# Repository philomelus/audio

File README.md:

# audio
Various audio circuits I've drawn up, almost exclusively found elsewhere.

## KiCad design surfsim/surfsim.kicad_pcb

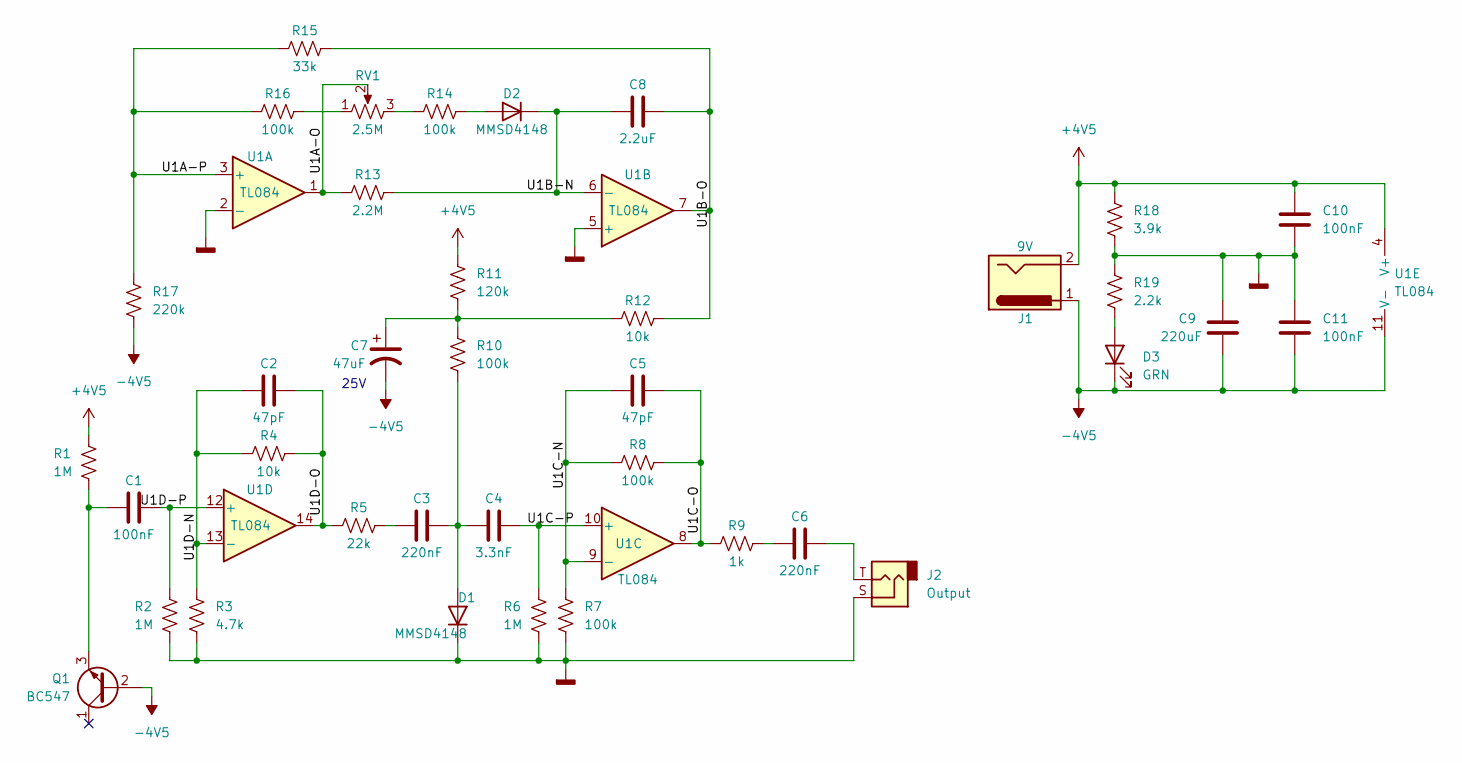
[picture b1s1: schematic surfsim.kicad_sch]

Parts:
C1, C10, C11: 100nF; C_0805_2012Metric_Pad1.18x1.45mm_HandSolder
C2, C5: 47pF; C_0805_2012Metric_Pad1.18x1.45mm_HandSolder
C3, C6: 220nF; C_0805_2012Metric_Pad1.18x1.45mm_HandSolder
C4: 3.3nF; C_0805_2012Metric_Pad1.18x1.45mm_HandSolder
C7: 47uF; C_0805_2012Metric_Pad1.18x1.45mm_HandSolder
C8: 2.2uF; C_0805_2012Metric_Pad1.18x1.45mm_HandSolder
C9: 220uF; C_0805_2012Metric_Pad1.18x1.45mm_HandSolder
D1, D2: MMSD4148; D_SOD-123
D3: GRN; D_1206_3216Metric_Pad1.42x1.75mm_HandSolder
J1: 9V; BarrelJack_CUI_PJ-036AH-SMT_Horizontal
J2: Output; Jack_3.5mm_CUI_MJ-3523-SMT
Q1: BC547; TO-92_Inline
R1, R2, R6: 1M; R_0805_2012Metric_Pad1.20x1.40mm_HandSolder
R3: 4.7k; R_0805_2012Metric_Pad1.20x1.40mm_HandSolder
R4, R12: 10k; R_0805_2012Metric_Pad1.20x1.40mm_HandSolder
R5: 22k; R_0805_2012Metric_Pad1.20x1.40mm_HandSolder
R7, R8, R10, R14, R16: 100k; R_0805_2012Metric_Pad1.20x1.40mm_HandSolder
R9: 1k; R_0805_2012Metric_Pad1.20x1.40mm_HandSolder
R11: 120k; R_0805_2012Metric_Pad1.20x1.40mm_HandSolder
R13: 2.2M; R_0805_2012Metric_Pad1.20x1.40mm_HandSolder
R15: 33k; R_0805_2012Metric_Pad1.20x1.40mm_HandSolder
R17: 220k; R_0805_2012Metric_Pad1.20x1.40mm_HandSolder
R18: 3.9k; R_0805_2012Metric_Pad1.20x1.40mm_HandSolder
R19: 2.2k; R_0805_2012Metric_Pad1.20x1.40mm_HandSolder
RV1: 2.5M; SolderWire-0.1sqmm_1x03_P3.6mm_D0.4mm_OD1mm
U1: TL084; SOIC-14_3.9x8.7mm_P1.27mm

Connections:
+4V5: C10.1, J1.2, R1.1, R11.1, R18.1, U1.4 (V+)
-4V5: C7.2, C9.2, C11.2, D3.1 (K), J1.1, Q1.2 (B), R17.2, U1.11 (V-)
/U1A-O: R13.1, RV1.2, U1.1
/U1A-P: R15.1, R16.1, R17.1, U1.3 (+)
/U1B-N: C8.1, D2.1 (K), R13.2, U1.6 (-)
/U1B-O: C8.2, R12.2, R15.2, U1.7
/U1C-N: C5.1, R7.1, R8.1, U1.9 (-)
/U1C-O: C5.2, R8.2, R9.1, U1.8
/U1C-P: C4.2, R6.1, U1.10 (+)
/U1D-N: C2.1, R3.1, R4.1, U1.13 (-)
/U1D-O: C2.2, R4.2, R5.1, U1.14
/U1D-P: C1.2, R2.1, U1.12 (+)
GNDD: C9.1, C10.2, C11.1, D1.1 (K), J2.S, R2.2, R3.2, R6.2, R7.2, R18.2, R19.1, U1.2 (-), U1.5 (+)
unnamed: C1.1, Q1.3 (E), R1.2
unnamed: C3.1, R5.2
unnamed: C3.2, C4.1, D1.2 (A), R10.2
unnamed: C6.1, R9.2
unnamed: C6.2, J2.T
unnamed: C7.1, R10.1, R11.2, R12.1
unnamed: D2.2 (A), R14.2
unnamed: D3.2 (A), R19.2
unnamed: R14.1, RV1.3
unnamed: R16.2, RV1.1

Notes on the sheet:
25V

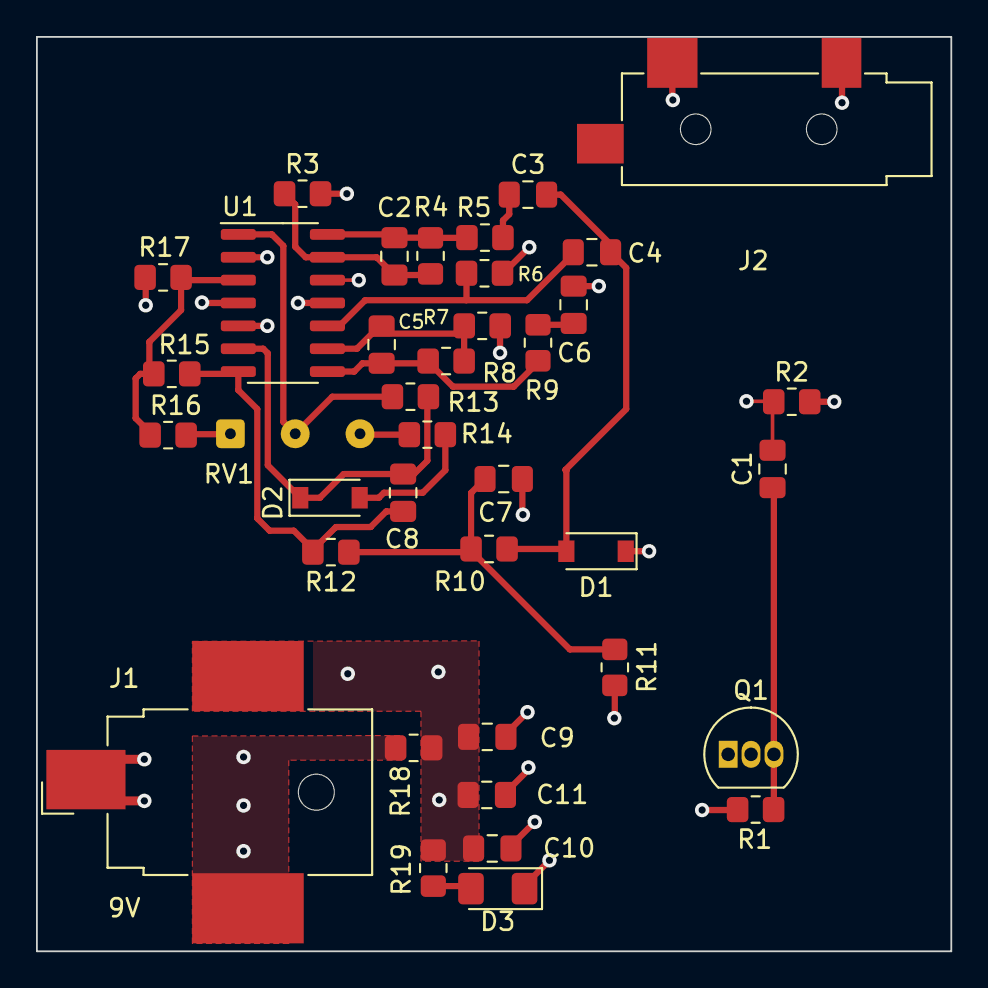
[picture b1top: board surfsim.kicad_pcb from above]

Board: 4 copper layers, 50.8 x 50.8 mm, 38 parts (0 on the bottom side), 23 nets.

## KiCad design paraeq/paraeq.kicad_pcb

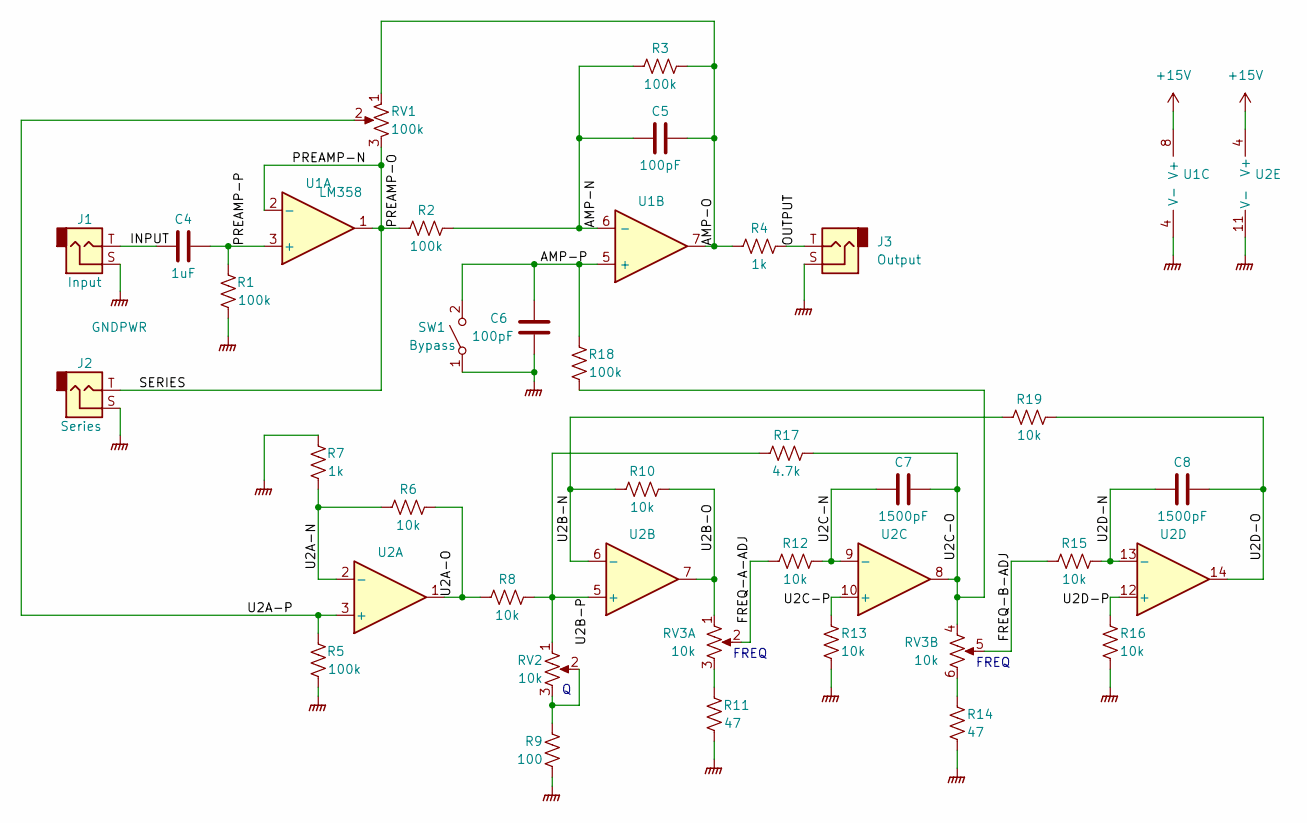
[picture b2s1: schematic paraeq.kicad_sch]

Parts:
C4: 1uF; C_0805_2012Metric_Pad1.18x1.45mm_HandSolder
C5, C6: 100pF; C_0805_2012Metric_Pad1.18x1.45mm_HandSolder
C7, C8: 1500pF; C_0805_2012Metric_Pad1.18x1.45mm_HandSolder
J1: Input; Jack_3.5mm_CUI_SJ1-3523N_Horizontal
J2: Series; Jack_3.5mm_CUI_SJ1-3523N_Horizontal
J3: Output; Jack_3.5mm_CUI_SJ1-3523N_Horizontal
R1, R2, R3, R5, R18: 100k; R_0805_2012Metric_Pad1.20x1.40mm_HandSolder
R4, R7: 1k; R_0805_2012Metric_Pad1.20x1.40mm_HandSolder
R6, R8, R10, R12, R13, R15, R16, R19: 10k; R_0805_2012Metric_Pad1.20x1.40mm_HandSolder
R9: 100; R_0805_2012Metric_Pad1.20x1.40mm_HandSolder
R11, R14: 47; R_0805_2012Metric_Pad1.20x1.40mm_HandSolder
R17: 4.7k; R_0805_2012Metric_Pad1.20x1.40mm_HandSolder
RV1: 100k; SolderWire-0.1sqmm_1x03_P3.6mm_D0.4mm_OD1mm
RV2: 10k; SolderWire-0.1sqmm_1x03_P3.6mm_D0.4mm_OD1mm
RV3: 10k; SolderWire-0.1sqmm_2x03_P3.6mm_D0.4mm_OD1mm
SW1: Bypass; SolderWire-0.1sqmm_1x02_P3.6mm_D0.4mm_OD1mm
U1: LM358; SOIC-8_3.9x4.9mm_P1.27mm
U2: LM324; SOIC-14_3.9x8.7mm_P1.27mm

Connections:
+15V: U1.8 (V+), U2.4 (V+); also elsewhere on the board
/AMP-N: C5.1, R2.2, R3.1, U1.6 (-)
/AMP-O: C5.2, R3.2, R4.1, RV1.1, U1.7
/AMP-P: C6.1, R18.1, SW1.2 (B), U1.5 (+)
/FREQ-A-ADJ: R12.1, RV3.2
/FREQ-B-ADJ: R15.1, RV3.5
/INPUT: C4.1, J1.T
/OUTPUT: J3.T, R4.2
/PREAMP-P: C4.2, R1.1, U1.3 (+)
/SERIES: J2.T, R2.1, RV1.3, U1.1, U1.2 (-)
/U2A-N: R6.1, R7.2, U2.2 (-)
/U2A-O: R6.2, R8.1, U2.1
/U2A-P: R5.1, RV1.2, U2.3 (+)
/U2B-N: R10.1, R19.1, U2.6 (-)
/U2B-O: R10.2, RV3.1, U2.7
/U2B-P: R8.2, R17.1, RV2.1, U2.5 (+)
/U2C-N: C7.1, R12.2, U2.9 (-)
/U2C-O: C7.2, R17.2, R18.2, RV3.4, U2.8
/U2C-P: R13.1, U2.10 (+)
/U2D-N: C8.1, R15.2, U2.13 (-)
/U2D-O: C8.2, R19.2, U2.14
/U2D-P: R16.1, U2.12 (+)
GNDPWR: C6.2, J1.R, J1.S, J2.R, J2.S, J3.R, J3.S, R1.2, R5.2, R7.1, R9.2, R11.2, R13.2, R14.2, R16.2, SW1.1 (A), U1.4 (V-), U2.11 (V-); also elsewhere on the board
unnamed: R9.1, RV2.2, RV2.3
unnamed: R11.1, RV3.3
unnamed: R14.1, RV3.6

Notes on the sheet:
FREQ

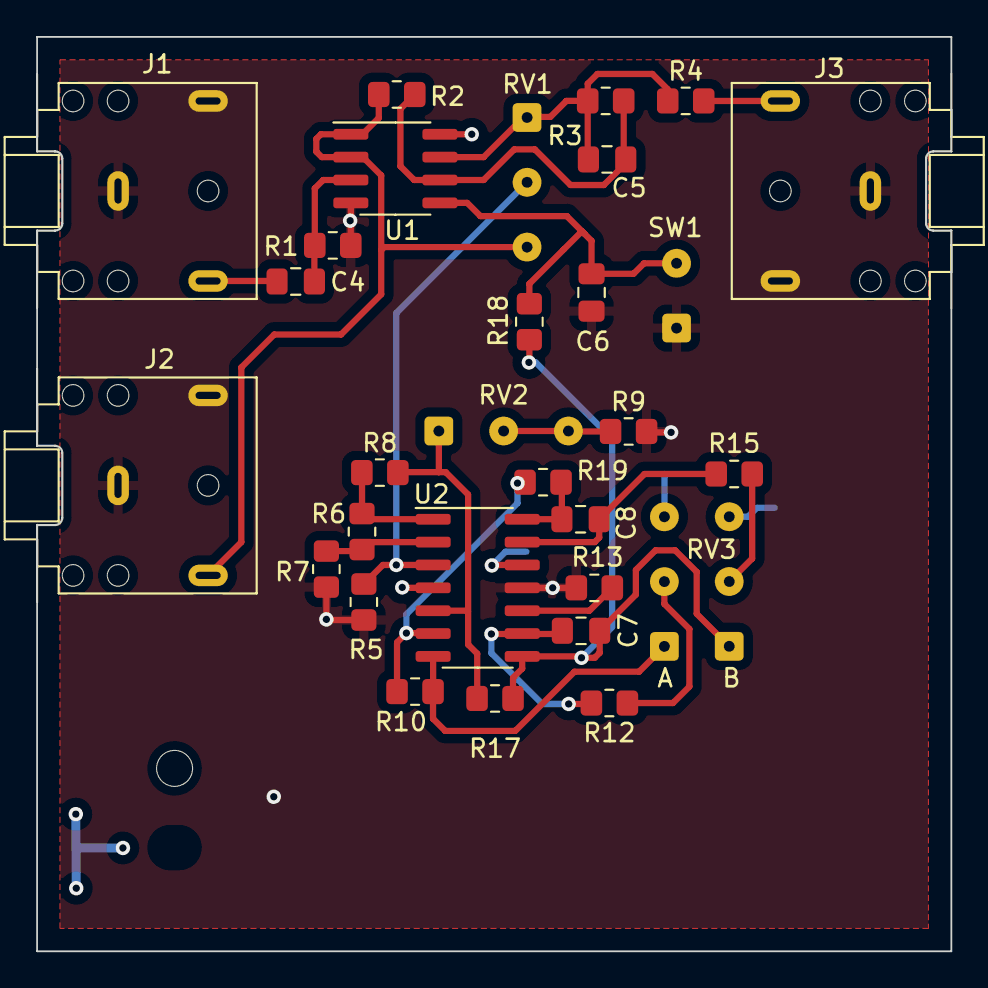
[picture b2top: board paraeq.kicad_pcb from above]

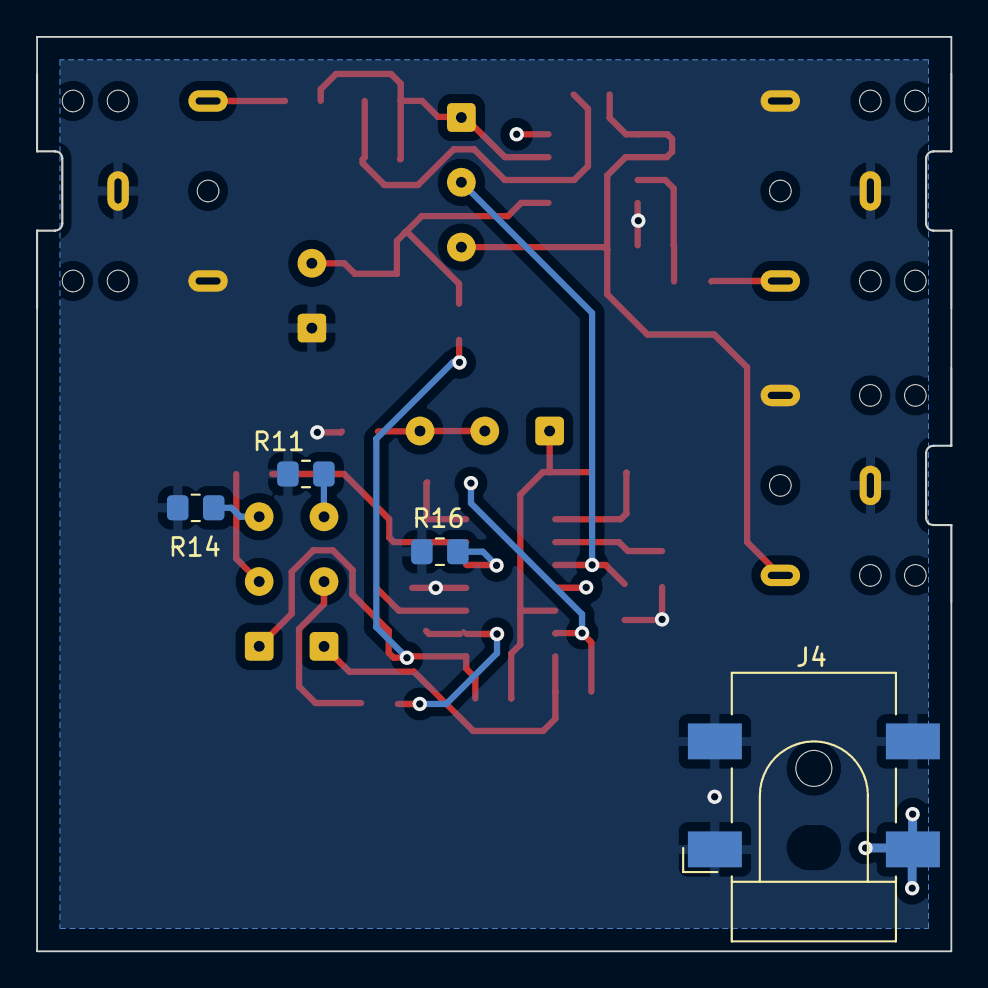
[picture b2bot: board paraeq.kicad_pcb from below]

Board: 4 copper layers, 50.8 x 50.8 mm, 34 parts (4 on the bottom side), 26 nets.

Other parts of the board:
J4: BarrelJack_CLIFF_FC681465S_SMT_Horizontal

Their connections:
+15V: J4.3; also elsewhere on the board
GNDPWR: J4.1, J4.2; also elsewhere on the board

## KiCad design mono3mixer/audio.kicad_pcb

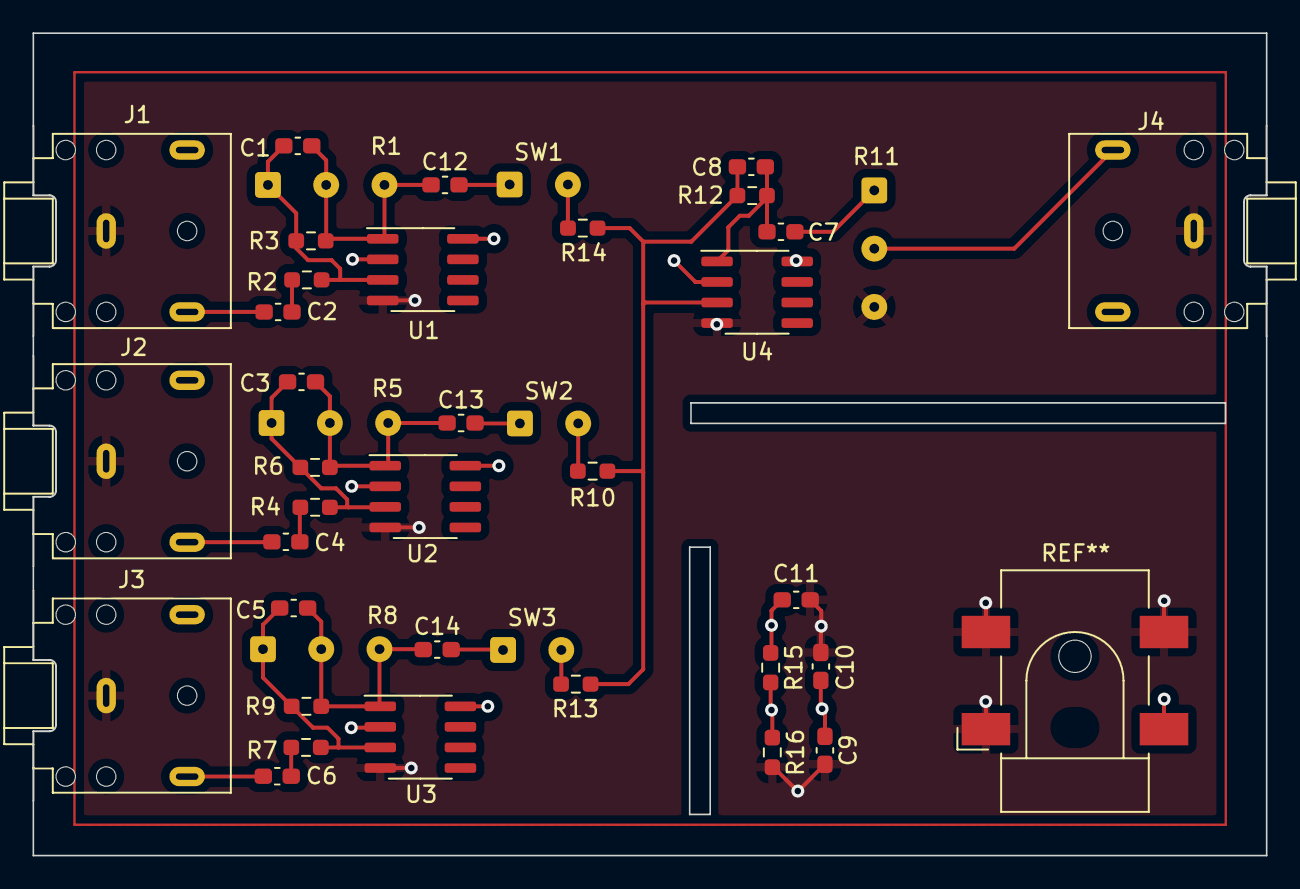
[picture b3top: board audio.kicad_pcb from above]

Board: 4 copper layers, 76.2 x 50.8 mm, 41 parts (0 on the bottom side), 25 nets.

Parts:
C1, C3, C5: 15p; C_0603_1608Metric_Pad1.08x0.95mm_HandSolder
C2, C4, C6, C7, C8, C9, C12, C13, C14: 0.2u; C_0603_1608Metric_Pad1.08x0.95mm_HandSolder
C10, C11: 100u; C_0603_1608Metric_Pad1.08x0.95mm_HandSolder
J1, J2, J3, J4: AudioJack2; Jack_3.5mm_CUI_SJ1-3523N_Horizontal
R1, R5, R8: 500K; SolderWire-0.1sqmm_1x03_P3.6mm_D0.4mm_OD1mm
R2, R4, R7: 47k; R_0603_1608Metric_Pad0.98x0.95mm_HandSolder
R3, R6, R9: 1M; R_0603_1608Metric_Pad0.98x0.95mm_HandSolder
R10, R13, R14: 10k; R_0603_1608Metric_Pad0.98x0.95mm_HandSolder
R11: 100k; SolderWire-0.1sqmm_1x03_P3.6mm_D0.4mm_OD1mm
R12, R15, R16: 100k; R_0603_1608Metric_Pad0.98x0.95mm_HandSolder
SW1, SW2, SW3: SW_SPST; SolderWire-0.1sqmm_1x02_P3.6mm_D0.4mm_OD1mm
U1, U2, U3, U4: RC4560; SOIC-8_3.9x4.9mm_P1.27mm

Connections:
+12V: C11.2, R15.1, U1.8 (V+), U2.8 (V+), U3.8 (V+), U4.8 (V+)
/Input 1/Out: C8.1, R10.2, R12.1, R13.2, R14.2, U4.3 (+)
/Vb: C9.1, C10.1, R15.2, R16.1, U1.2 (-), U2.2 (-), U3.2 (-), U4.2 (-)
GNDREF: C9.2, C10.2, C11.1, J1.S, J2.S, J3.S, J4.S, R11.3, R16.2, U1.4 (V-), U2.4 (V-), U3.4 (V-), U4.4 (V-)
unnamed: C1.1, R1.1, R2.2, R3.1, U1.3 (+)
unnamed: C1.2, C12.1, R1.2, R1.3, R3.2, U1.1
unnamed: C2.1, J1.T
unnamed: C2.2, R2.1
unnamed: C3.1, R4.2, R5.1, R6.1, U2.3 (+)
unnamed: C4.1, J2.T
unnamed: C4.2, R4.1
unnamed: C5.1, R7.2, R8.1, R9.1, U3.3 (+)
unnamed: C6.1, J3.T
unnamed: C6.2, R7.1
unnamed: C7.1, C8.2, R12.2, U4.1
unnamed: C7.2, R11.1
unnamed: C12.2, SW1.1 (A)
unnamed: C3.2, C13.1, R5.2, R5.3, R6.2, U2.1
unnamed: C13.2, SW2.1 (A)
unnamed: C5.2, C14.1, R8.2, R8.3, R9.2, U3.1
unnamed: C14.2, SW3.1 (A)
unnamed: J4.T, R11.2
unnamed: R10.1, SW2.2 (B)
unnamed: R13.1, SW3.2 (B)
unnamed: R14.1, SW1.2 (B)

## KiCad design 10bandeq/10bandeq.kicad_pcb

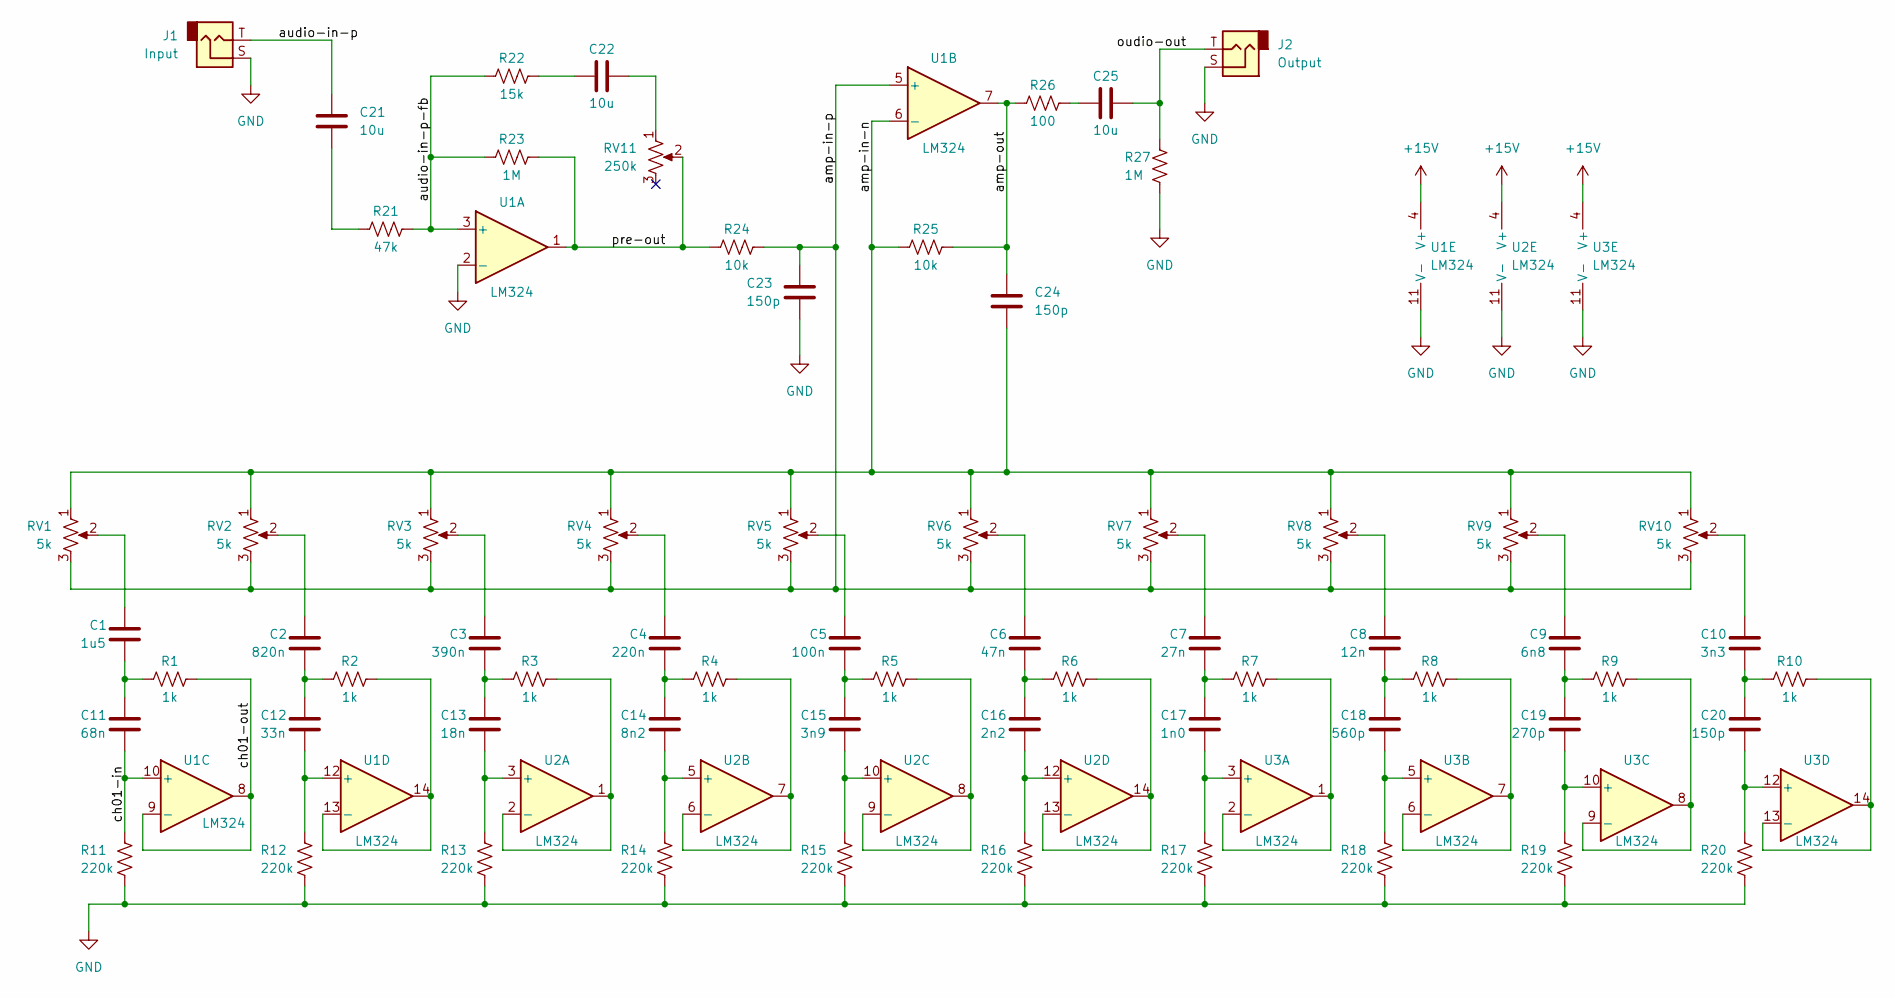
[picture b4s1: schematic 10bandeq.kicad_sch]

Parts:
C1: 1u5; C_0805_2012Metric_Pad1.18x1.45mm_HandSolder
C2: 820n; C_0805_2012Metric_Pad1.18x1.45mm_HandSolder
C3: 390n; C_0805_2012Metric_Pad1.18x1.45mm_HandSolder
C4: 220n; C_0805_2012Metric_Pad1.18x1.45mm_HandSolder
C5: 100n; C_0805_2012Metric_Pad1.18x1.45mm_HandSolder
C6: 47n; C_0805_2012Metric_Pad1.18x1.45mm_HandSolder
C7: 27n; C_0805_2012Metric_Pad1.18x1.45mm_HandSolder
C8: 12n; C_0805_2012Metric_Pad1.18x1.45mm_HandSolder
C9: 6n8; C_0805_2012Metric_Pad1.18x1.45mm_HandSolder
C10: 3n3; C_0805_2012Metric_Pad1.18x1.45mm_HandSolder
C11: 68n; C_0805_2012Metric_Pad1.18x1.45mm_HandSolder
C12: 33n; C_0805_2012Metric_Pad1.18x1.45mm_HandSolder
C13: 18n; C_0805_2012Metric_Pad1.18x1.45mm_HandSolder
C14: 8n2; C_0805_2012Metric_Pad1.18x1.45mm_HandSolder
C15: 3n9; C_0805_2012Metric_Pad1.18x1.45mm_HandSolder
C16: 2n2; C_0805_2012Metric_Pad1.18x1.45mm_HandSolder
C17: 1n0; C_0805_2012Metric_Pad1.18x1.45mm_HandSolder
C18: 560p; C_0805_2012Metric_Pad1.18x1.45mm_HandSolder
C19: 270p; C_0805_2012Metric_Pad1.18x1.45mm_HandSolder
C20, C23, C24: 150p; C_0805_2012Metric_Pad1.18x1.45mm_HandSolder
C21, C22, C25: 10u; C_0805_2012Metric_Pad1.18x1.45mm_HandSolder
J1: Input; Jack_3.5mm_CUI_SJ1-3523N_Horizontal
J2: Output; Jack_3.5mm_CUI_SJ1-3523N_Horizontal
R1, R2, R3, R4, R5, R6, R7, R8, R9, R10: 1k; R_0805_2012Metric_Pad1.20x1.40mm_HandSolder
R11, R12, R13, R14, R15, R16, R17, R18, R19, R20: 220k; R_0805_2012Metric_Pad1.20x1.40mm_HandSolder
R21: 47k; R_0805_2012Metric_Pad1.20x1.40mm_HandSolder
R22: 15k; R_0805_2012Metric_Pad1.20x1.40mm_HandSolder
R23, R27: 1M; R_0805_2012Metric_Pad1.20x1.40mm_HandSolder
R24, R25: 10k; R_0805_2012Metric_Pad1.20x1.40mm_HandSolder
R26: 100; R_0805_2012Metric_Pad1.20x1.40mm_HandSolder
RV1, RV2, RV3, RV4, RV5, RV6, RV7, RV8, RV9, RV10: 5k; SolderWire-0.1sqmm_1x03_P3.6mm_D0.4mm_OD1mm
RV11: 250k; SolderWire-0.1sqmm_1x02_P3.6mm_D0.4mm_OD1mm
U1, U2, U3: LM324; SO-14_3.9x8.65mm_P1.27mm

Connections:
+15V: U1.4 (V+), U2.4 (V+), U3.4 (V+); also elsewhere on the board
/amp-in-n: C24.2, R25.1, RV1.1, RV2.1, RV3.1, RV4.1, RV5.1, RV6.1, RV7.1, RV8.1, RV9.1, RV10.1, U1.6 (-)
/amp-in-p: C23.1, R24.2, RV1.3, RV2.3, RV3.3, RV4.3, RV5.3, RV6.3, RV7.3, RV8.3, RV9.3, RV10.3, U1.5 (+)
/amp-out: C24.1, R25.2, R26.1, U1.7
/audio-in-p: C21.1, J1.T; also elsewhere on the board
/audio-in-p-fb: R21.2, R22.1, R23.1, U1.3 (+)
/ch01-in: C11.2, R11.2, U1.10 (+)
/ch01-out: R1.2, U1.8, U1.9 (-)
/oudio-out: C25.2, J2.T, R27.1; also elsewhere on the board
/pre-out: R23.2, R24.1, RV11.2, U1.1
GND: C23.2, J1.S, J2.S, R11.1, R12.1, R13.1, R14.1, R15.1, R16.1, R17.1, R18.1, R19.1, R20.1, R27.2, U1.2 (-), U1.11 (V-), U2.11 (V-), U3.11 (V-); also elsewhere on the board
unnamed: C1.1, RV1.2
unnamed: C1.2, C11.1, R1.1
unnamed: C3.1, RV3.2
unnamed: C4.2, C14.1, R4.1
unnamed: C5.2, C15.1, R5.1
unnamed: C6.1, RV6.2
unnamed: C6.2, C16.1, R6.1
unnamed: C7.1, RV7.2
unnamed: C7.2, C17.1, R7.1
unnamed: C8.1, RV8.2
unnamed: C9.1, RV9.2
unnamed: C2.2, C12.1, R2.1
unnamed: C12.2, R12.2, U1.12 (+)
unnamed: C3.2, C13.1, R3.1
unnamed: C13.2, R13.2, U2.3 (+)
unnamed: C8.2, C18.1, R8.1
unnamed: C9.2, C19.1, R9.1
unnamed: C19.2, R19.2, U3.10 (+)
unnamed: R6.2, U2.13 (-), U2.14
unnamed: R7.2, U3.1, U3.2 (-)
unnamed: R9.2, U3.8, U3.9 (-)
unnamed: C10.2, C20.1, R10.1
unnamed: C14.2, R14.2, U2.5 (+)
unnamed: C17.2, R17.2, U3.3 (+)
unnamed: C18.2, R18.2, U3.5 (+)
unnamed: C21.2, R21.1
unnamed: C22.1, R22.2
unnamed: C25.1, R26.2
unnamed: C2.1, RV2.2
unnamed: C4.1, RV4.2
unnamed: C5.1, RV5.2
unnamed: C10.1, RV10.2
unnamed: C22.2, RV11.1
unnamed: R2.2, U1.13 (-), U1.14
unnamed: R3.2, U2.1, U2.2 (-)
unnamed: R4.2, U2.6 (-), U2.7
unnamed: R5.2, U2.8, U2.9 (-)
unnamed: C15.2, R15.2, U2.10 (+)
unnamed: C16.2, R16.2, U2.12 (+)
unnamed: R8.2, U3.6 (-), U3.7
unnamed: C20.2, R20.2, U3.12 (+)
unnamed: R10.2, U3.13 (-), U3.14

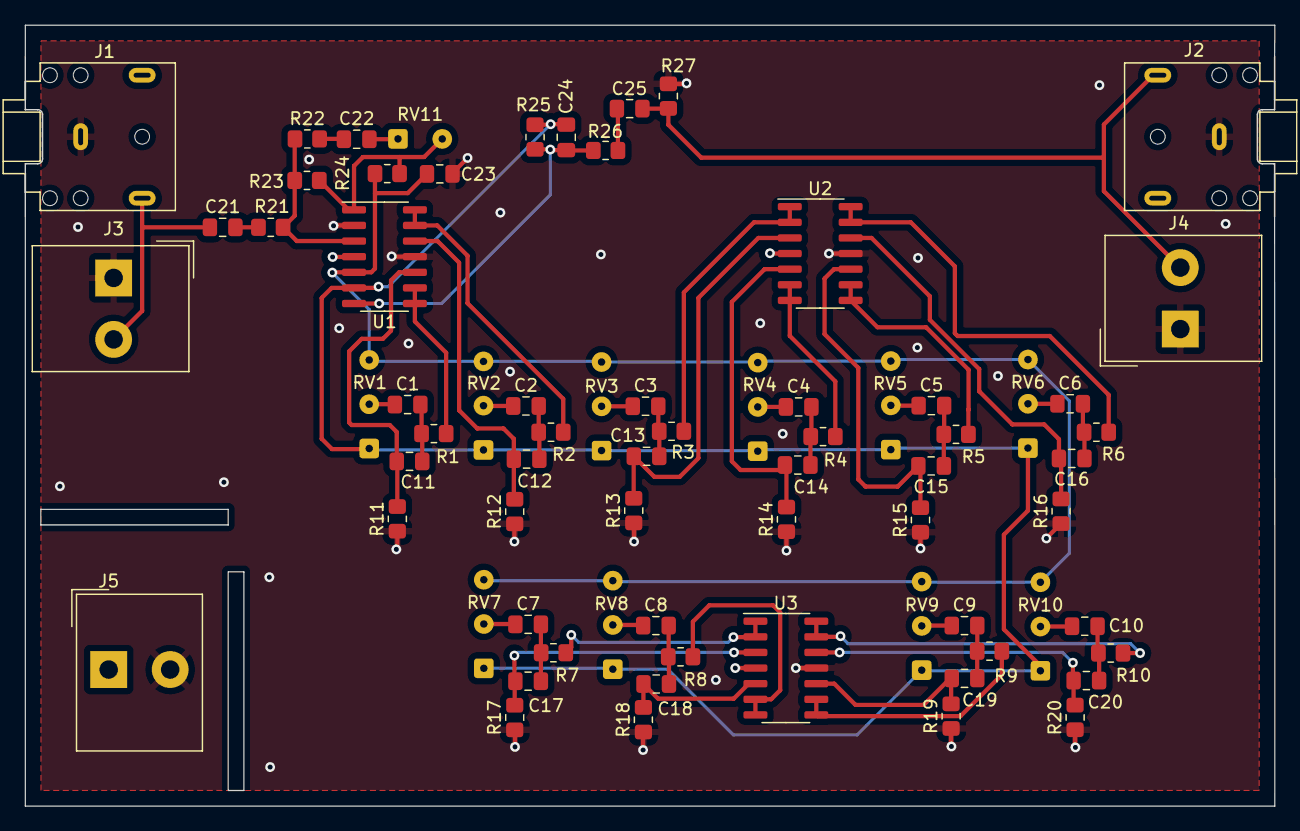
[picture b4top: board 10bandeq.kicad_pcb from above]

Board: 4 copper layers, 101.6 x 63.5 mm, 71 parts (0 on the bottom side), 53 nets.

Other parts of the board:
J3: Input; Altech_AK300_1x02_P5.00mm_45-Degree
J4: Output; Altech_AK300_1x02_P5.00mm_45-Degree
J5: Power; Altech_AK300_1x02_P5.00mm_45-Degree

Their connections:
+15V: J5.1; also elsewhere on the board
/audio-in-p: J3.2; also elsewhere on the board
/oudio-out: J4.2; also elsewhere on the board
GND: J3.1, J4.1, J5.2; also elsewhere on the board

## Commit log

2022-10-14 Added gitignore for kicad.
2022-10-14 Added libs/.
2022-10-14 Adde models/.
2022-10-14 Added 10 band graphics equalizer.
2022-10-14 Added mono 3 mono input mixer.
2022-10-14 Added parametric equalizer. Not complete.
2022-10-14 Added readme.
2022-10-14 Finished parametric equalizer.
2022-10-17 Finished surfsim capture and layout.
